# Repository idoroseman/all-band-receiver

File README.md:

Dear All-Band Receiver Enthusiasts,
-----------------------------------

First and foremost, I want to express my heartfelt gratitude for the overwhelming response to my recent article on the all-band receiver. Your interest and enthusiasm have truly exceeded my expectations. When I published the article, I had no idea it would garner such a high turnout of comments and support.

Unfortunately, I wasn't expecting such a turnout, as I only had a couple of spare PCBs on hand. However, I have some great news! I’ll be producing more boards, which will incorporate the future enhancements described in [the article](https://idoroseman.com/how-to-use-an-all-band-receiver-to-listen-to-airplane-pilot-communications-with-ground-controllers/) and will be available for purchase online in a few weeks. 
You’ll have the option to buy the PCB on its own or as part of a kit that includes a 3D-printed enclosure.

For those who prefer a DIY approach, I’ve uploaded all the necessary files to a GitHub repository, so you can get started on your own build. You can find the repository [here](https://github.com/idoroseman/all-band-receiver).

I also want to take a moment to thank the [original authors](https://techlib.com/electronics/allband.htm) who made this project possible: Charles Wenzel and Paul Beaumont (G7VAK). Their foundational work was instrumental in inspiring this project.

If you have any comments, suggestions, or ideas, please don’t hesitate to reach out. I’d love to hear your feedback and thoughts. You can email me at ido.roseman@gmail.com.

Thank you once again for your incredible support. Stay tuned for updates on the boards’ availability and other exciting developments!

Best regards,
Ido Roseman
[idoroseman.com](https://idoroseman.com/)

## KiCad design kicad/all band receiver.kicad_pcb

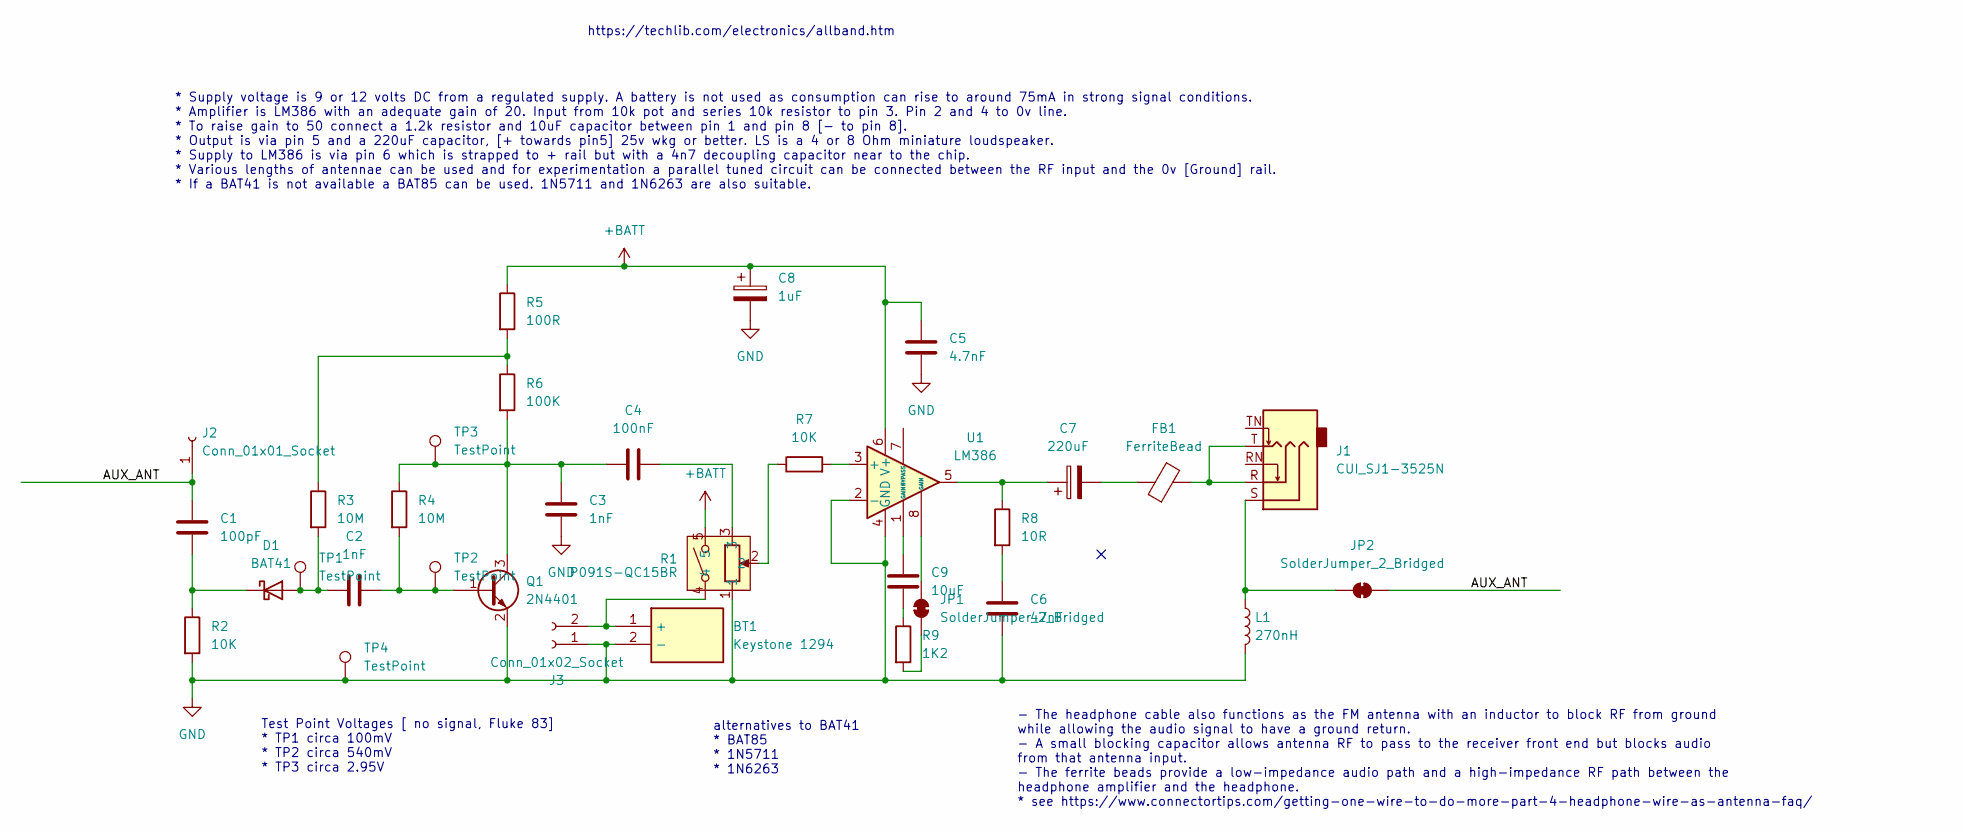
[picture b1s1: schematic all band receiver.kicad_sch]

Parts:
BT1: Keystone 1294; keystone 1294; Mouser Part Number 534-1294
C1: 100pF; C_0805_2012Metric_Pad1.18x1.45mm_HandSolder; Mouser Part Number 80-C0805C101K1HACTU; DigiKey Part Number 399-C0805C101J5GACTUCT-ND
C2, C3: 1nF; C_0805_2012Metric_Pad1.18x1.45mm_HandSolder; Mouser Part Number 187-CL21B102KBANNND; DigiKey Part Number 399-C0805C102K5RACTUCT-ND
C4: 100nF; C_0805_2012Metric_Pad1.18x1.45mm_HandSolder; Mouser Part Number 187-CL21B104MACNNNC; DigiKey Part Number 311-1140-1-ND
C5: 4.7nF; C_0805_2012Metric_Pad1.18x1.45mm_HandSolder; Mouser Part Number 791-0805N472J500CT; DigiKey Part Number 311-1133-1-ND
C6: 47nF; C_0805_2012Metric_Pad1.18x1.45mm_HandSolder; Mouser Part Number 791-0805B473J500CT; DigiKey Part Number 399-C0805C473K5RACTUCT-ND
C7: 220uF; CP_Elec_6.3x5.4; Mouser Part Number 140-VZL221M1CTR-0607; DigiKey Part Number 478-APA0608221M010RCT-ND
C8: 1uF; CP_Elec_4x5.3; Mouser Part Number 710-865060640001; DigiKey Part Number 732-6401-1-ND
C9: 10uF; C_0805_2012Metric_Pad1.18x1.45mm_HandSolder; Mouser Part Number 187-CL21A106KQFNFNE; DigiKey Part Number 587-1300-1-ND
D1: BAT41; D_SOD-123; Mouser Part Number 511-BAT41ZFILM; DigiKey Part Number 497-5558-1-ND
FB1: FerriteBead; L_0805_2012Metric_Pad1.15x1.40mm_HandSolder; Mouser Part Number 70-ILBB0805ER110V; DigiKey Part Number MH2029-070YCT-ND
J1: CUI_SJ1-3525N; Jack_3.5mm_CUI_SJ1-3525N_Horizontal; Mouser Part Number 490-SJ1-3525NG-GR; DigiKey Part Number SJ1-3525NG
J2: Conn_01x01_Socket; PinHeader_1x01_P2.54mm_Horizontal
J3: Conn_01x02_Socket; PinSocket_1x02_P2.54mm_Vertical
JP1, JP2: SolderJumper_2_Bridged; SolderJumper-2_P1.3mm_Bridged_RoundedPad1.0x1.5mm
L1: 270nH; L_0805_2012Metric_Pad1.15x1.40mm_HandSolder; Mouser Part Number 70-IMC0805ERR27J01; DigiKey Part Number 118-CE201210-R27JCT-ND
Q1: 2N4401; SOT-23; Mouser Part Number 637-MMBT4401; DigiKey Part Number 4786-MMBT4401CT-ND
R1: P091S-QC15BR; Mouser Part Number 858-P091SFC20BR10K; DigiKey Part Number 987-1284-ND
R2, R7: 10K; R_0805_2012Metric_Pad1.20x1.40mm_HandSolder; Mouser Part Number 71-CRCW0805-10K-E3; DigiKey Part Number P10KACT-ND
R3, R4: 10M; R_0805_2012Metric_Pad1.20x1.40mm_HandSolder; Mouser Part Number 603-RC0805FR-0710ML; DigiKey Part Number P10MACT-ND
R5: 100R; R_0805_2012Metric_Pad1.20x1.40mm_HandSolder; Mouser Part Number 603-AC0805FR-7W100RL; DigiKey Part Number P100ACT-ND
R6: 100K; R_0805_2012Metric_Pad1.20x1.40mm_HandSolder; Mouser Part Number 652-CR0805FX-1003ELF; DigiKey Part Number P100KACT-ND
R8: 10R; R_0805_2012Metric_Pad1.20x1.40mm_HandSolder; Mouser Part Number 603-AC0805JR-0710RL; DigiKey Part Number RMCF0805JT10R0CT-ND
R9: 1K2; R_0805_2012Metric_Pad1.20x1.40mm_HandSolder; Mouser Part Number 652-CR0805FX-1201ELF; DigiKey Part Number A126346CT-ND
TP1, TP2, TP3: TestPoint; TestPoint_Pad_D1.5mm
TP4: TestPoint; TestPoint_Pad_2.0x2.0mm
U1: LM386; SOIC-8_3.9x4.9mm_P1.27mm; Mouser Part Number 926-LM386MX-1/NOPB; DigiKey Part Number LM386MX-1/NOPBCT-ND

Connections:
+BATT: C5.2, C8.1, R1.5, R5.1, U1.6 (V+)
/AUX_ANT: C1.1, J2.1, JP2.1 (A)
GND: BT1.2 (-), C3.2, C5.1, C6.1, C8.2, J3.1, L1.2, Q1.2 (E), R1.1, R2.2, TP4.1, U1.2 (-), U1.4 (GND)
unnamed: BT1.1 (+), J3.2, R1.4
unnamed: C4.2, R1.3
unnamed: C6.2, R8.2
unnamed: C7.1, R8.1, U1.5
unnamed: C7.2, FB1.1
unnamed: C9.1, R9.1
unnamed: C9.2, U1.1 (GAIN)
unnamed: C2.1, D1.2 (A), R3.2, TP1.1
unnamed: C1.2, D1.1 (K), R2.1
unnamed: FB1.2, J1.R, J1.T
unnamed: JP1.1 (A), R9.2
unnamed: JP1.2 (B), U1.8 (GAIN)
unnamed: J1.S, JP2.2 (B), L1.1
unnamed: C2.2, Q1.1 (B), R4.2, TP2.1
unnamed: C3.1, C4.1, Q1.3 (C), R4.1, R6.2, TP3.1
unnamed: R1.2, R7.1
unnamed: R3.1, R5.2, R6.1
unnamed: R7.2, U1.3 (+)

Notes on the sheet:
﻿alternatives to BAT41 * BAT85 * 1N5711 * 1N6263
* Supply voltage is 9 or 12 volts DC from a regulated supply. A battery is not used as consumption can rise to around 75mA in strong signal conditions. * Amplifier is LM386 with an adequate gain of 20. Input from 10k pot and series 10k resistor to pin 3. Pin 2 and 4 to 0v line. * To raise gain to 5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
﻿Test Point Voltages [ no signal, Fluke 83] * TP1 circa 100mV * TP2 circa 540mV * TP3 circa 2.95V
https://techlib.com/electronics/allband.htm
- The headphone cable also functions as the FM antenna with an inductor to block RF from ground while allowing the audio signal to have a ground return. - A small blocking capacitor allows antenna RF to pass to the receiver front end but blocks audio from that antenna input. - The ferrite beads pro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

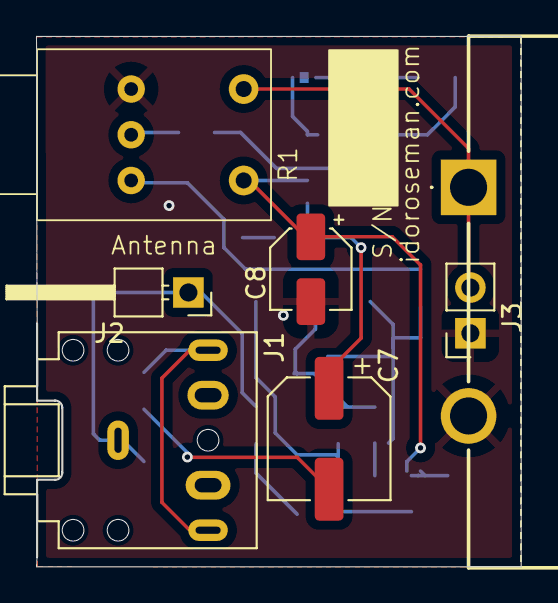
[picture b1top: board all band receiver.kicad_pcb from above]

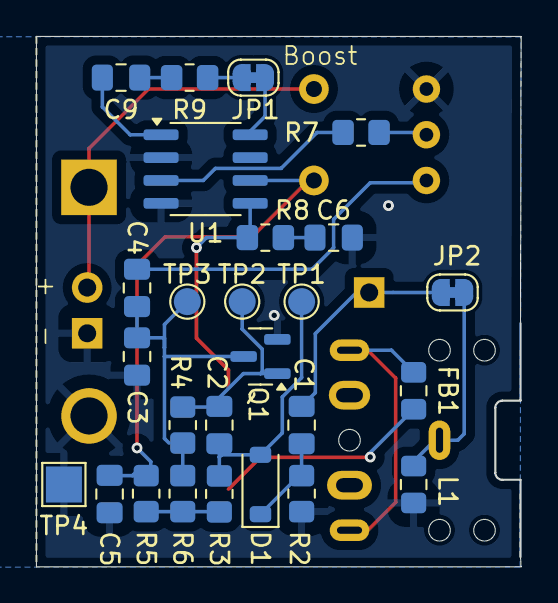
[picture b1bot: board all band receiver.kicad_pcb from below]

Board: 2 copper layers, 26.9 x 29.4 mm, 33 parts (26 on the bottom side), 21 nets.

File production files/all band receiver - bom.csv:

"Reference","Value","Datasheet","Footprint","Qty","DNP"
"BT1","Keystone 1294","https://www.keyelco.com/userAssets/file/m70p37.pdf","easyeda2kicad:keystone 1294","1",""
"C1","100pF","~","Capacitor_SMD:C_0805_2012Metric_Pad1.18x1.45mm_HandSolder","1",""
"C2,C3","1nF","~","Capacitor_SMD:C_0805_2012Metric_Pad1.18x1.45mm_HandSolder","2",""
"C4","100nF","~","Capacitor_SMD:C_0805_2012Metric_Pad1.18x1.45mm_HandSolder","1",""
"C5","4.7nF","~","Capacitor_SMD:C_0805_2012Metric_Pad1.18x1.45mm_HandSolder","1",""
"C6","47nF","~","Capacitor_SMD:C_0805_2012Metric_Pad1.18x1.45mm_HandSolder","1",""
"C7","220uF","~","Capacitor_SMD:CP_Elec_6.3x5.4","1",""
"C8","1uF","~","Capacitor_SMD:CP_Elec_4x5.3","1",""
"C9","10uF","~","Capacitor_SMD:C_0805_2012Metric_Pad1.18x1.45mm_HandSolder","1",""
"D1","BAT41","~","Diode_SMD:D_SOD-123","1",""
"FB1","FerriteBead","~","Inductor_SMD:L_0805_2012Metric_Pad1.15x1.40mm_HandSolder","1",""
"J1","AudioJack3_SwitchT","~","Connector_Audio:Jack_3.5mm_CUI_SJ-3524-SMT_Horizontal","1",""
"J2","Conn_01x01_Socket","~","Connector_Wire:SolderWire-0.5sqmm_1x01_D0.9mm_OD2.1mm","1",""
"J3","Conn_01x02_Socket","~","Connector_PinSocket_2.54mm:PinSocket_1x02_P2.54mm_Vertical","1","DNP"
"L1","270nH","~","Inductor_SMD:L_0805_2012Metric_Pad1.15x1.40mm_HandSolder","1",""
"Q1","2N4401","~","Package_TO_SOT_SMD:SOT-23","1",""
"R1","~","https://www.lcsc.com/datasheet/lcsc_datasheet_2311142111_TT-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","easyeda2kicad:P091S-QC15BR","1",""
"R2,R7","10K","~","Resistor_SMD:R_0805_2012Metric_Pad1.20x1.40mm_HandSolder","2",""
"R3,R4","10M","~","Resistor_SMD:R_0805_2012Metric_Pad1.20x1.40mm_HandSolder","2",""
"R5","100R","~","Resistor_SMD:R_0805_2012Metric_Pad1.20x1.40mm_HandSolder","1",""
"R6","100K","~","Resistor_SMD:R_0805_2012Metric_Pad1.20x1.40mm_HandSolder","1",""
"R8","10R","~","Resistor_SMD:R_0805_2012Metric_Pad1.20x1.40mm_HandSolder","1",""
"R9","1K2","~","Resistor_SMD:R_0805_2012Metric_Pad1.20x1.40mm_HandSolder","1",""
"TP1,TP2,TP3,TP4","TestPoint","~","-- mixed values --","4",""
"U1","LM386","http://www.ti.com/lit/ds/symlink/lm386.pdf","Package_SO:SOIC-8_3.9x4.9mm_P1.27mm","1",""

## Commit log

2025-01-12 added link to original authors
2025-01-12 moved (almost) all smt components to bottom side so manufacturing is cheaper. chanded audio connector on upper side to thruhole for easy soldering
2025-03-16 production
2025-03-23 increased thermal relief for easier soldering
